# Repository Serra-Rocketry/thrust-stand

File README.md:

# thrust-stand

## 📋 Sobre

Sistema embarcado baseado em ESP32 para monitoramento de testes estáticos de motores de foguetes, com aquisição de empuxo, pressão e temperatura em tempo real, armazenamento em cartão SD e comunicação via Serial/Bluetooth.

## 🚀 Quick Start

1. Clone o repositório

```bash
git clone https://github.com/Serra-Rocketry/thrust-stand.git
```

2. Monte o hardware conforme o [mapeamento de conexões](./docs/HARDWARE.md)
3. Instale a biblioteca `Pushbutton` (Pololu) na Arduino IDE e carregue `firmware/firmware.ino` no ESP32 (placa `ESP32 Dev Module`)
4. Calibre a célula de carga com o [app de calibração](./software/config-load-cell/README.md)
5. Antes do teste, envie `TARE` e, se quiser aliviar o ESP, `BT OFF` (ver [comandos](./docs/API.md))

## 📁 Estrutura do Projeto

```
├── 📂 docs/              # Documentação técnica detalhada
├── 📂 extras/            # Utilitários extras (ex.: configuração do rádio APC220)
├── 📂 firmware/          # Código do microcontrolador ESP32
├── 📂 hardware/          # Esquemáticos, PCBs e lista de componentes
├── 📂 software/          # Ferramentas de análise e interface
└── 📂 Legacy/            # Arquivos antigos que não são mais usados
```

## 🔧 Pré-requisitos

- Hardware: ESP32 DevKit V1, célula de carga + módulo ADS1256, sensor de pressão (com divisor resistivo), termopar tipo K + módulo MAX31855, módulo microSD (SPI), botão tátil (`GPIO33` para TARE), LED com resistor de limitação, buzzer
- Software: Arduino IDE 2.0+ (core ESP32) e Python 3.10+ para o app de calibração
- Bibliotecas: ver `docs/FIRMWARE.md`

## 📖 Documentação

- [Esquemático e Montagem](./docs/HARDWARE.md)
- [Firmware e Arquitetura](./docs/FIRMWARE.md)
- [Protocolos e API](./docs/API.md)
- [Calibração da Célula de Carga](./software/config-load-cell/README.md)
- [Troubleshooting](./docs/TROUBLESHOOTING.md)
- [Evolução da Estrutura (V1 a V3)](./docs/EVOLUÇÃO_CAIXA.md)
- [Detalhes da V3](./docs/V3_DETALHES.md)
- [Arquivos Legados](./Legacy/README.md)

## 🎯 Funcionalidades

- ✅ Aquisição de empuxo e pressão a 500 Hz com ADC de 24 bits (ADS1256)
- ✅ Temperatura com termopar tipo K (MAX31855)
- ✅ Armazenamento em cartão SD com arquivos sequenciais, sem perda de amostras (gravação em núcleo separado)
- ✅ Controle local por botão (TARE)
- ✅ LED de status de gravação no SD
- ✅ Comunicação (Serial, Bluetooth), com `BT OFF` para pausar a transmissão durante o teste
- ✅ Calibração persistente da célula de carga

## 📊 Dados de Teste

Os dados de testes estáticos de motores específicos são armazenados no repositório dedicado:
[motor](https://github.com/Serra-Rocketry/motor)

Este repositório (thrust-stand) contém apenas o sistema de aquisição. Os dados coletados durante os testes devem ser commitados no repositório `motor`.

## 🤝 Contribuindo

Este projeto segue as [Boas Práticas da Serra Rocketry](https://github.com/Serra-Rocketry/best-practices). Para contribuir:

1. Fork o projeto
2. Crie uma branch para sua feature (`git checkout -b feature/AmazingFeature`)
3. Commit suas mudanças (`git commit -m 'Add some AmazingFeature'`)
4. Push para a branch (`git push origin feature/AmazingFeature`)
5. Abra um Pull Request

## ✨ Autores

- Equipe Serra Rocketry - Desenvolvimento e documentação
- Contribuidores - [Lista de contribuidores](https://github.com/Serra-Rocketry/thrust-stand/graphs/contributors)

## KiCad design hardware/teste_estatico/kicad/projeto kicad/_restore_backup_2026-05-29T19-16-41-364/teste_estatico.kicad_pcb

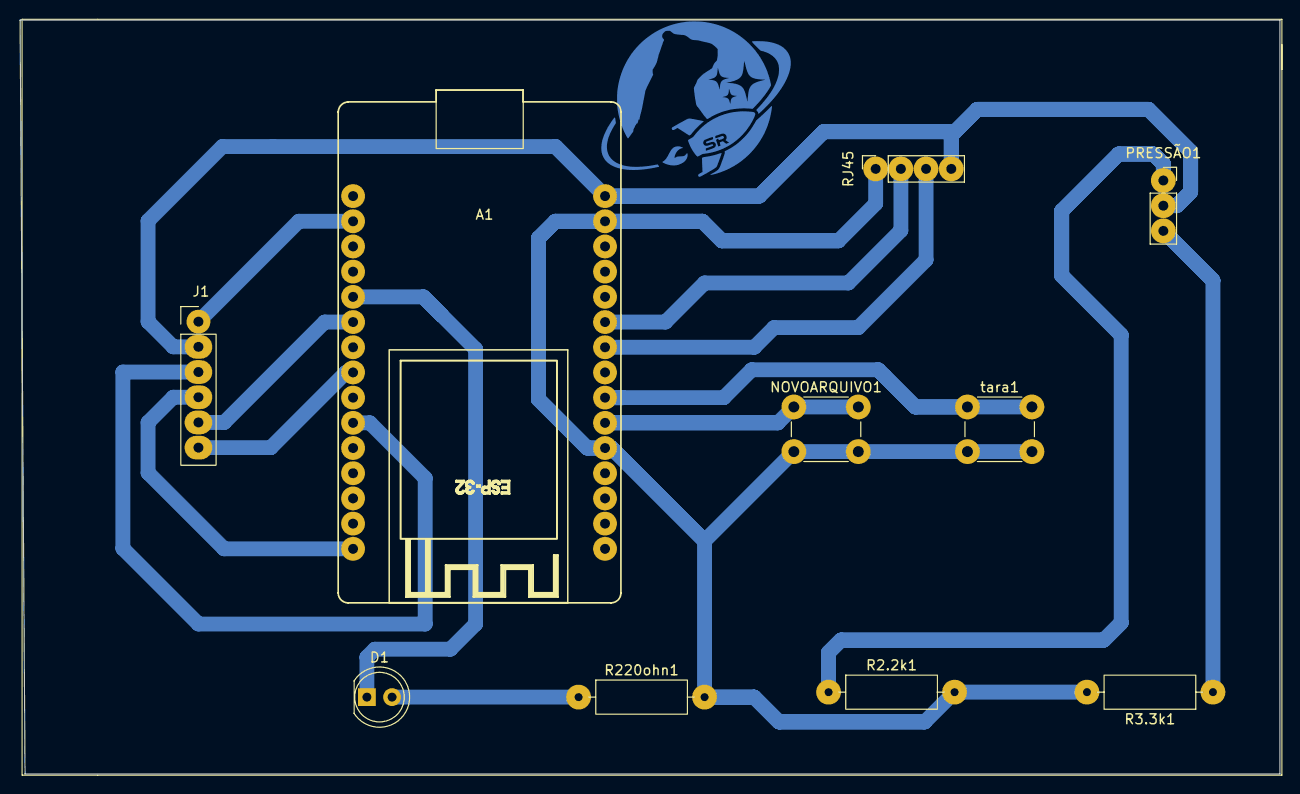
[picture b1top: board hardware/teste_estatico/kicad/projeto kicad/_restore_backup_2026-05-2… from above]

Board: 2 copper layers, 127.0 x 76.0 mm, 10 parts (0 on the bottom side), 14 nets.

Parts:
A1: ESP32_DevKit_V1_DOIT_30GPIOs; DOIT_ESP32_DEVKIT_30Pins
D1: LED; LED_D5.0mm_FlatTop
J1: PINHD_1x6_Female; PinSocket_1x06_P2.54mm_Vertical
NOVOARQUIVO1: Push_Button; SW_PUSH_6mm
PRESSÃO1: Sensor de pressão; PinSocket_1x03_P2.54mm_Vertical
R2.2k1, R3.3k1, R220ohn1: R; R_Axial_DIN0309_L9.0mm_D3.2mm_P12.70mm_Horizontal
RJ45: conexão do rj45; PinSocket_1x04_P2.54mm_Vertical
tara1: Push_Button; SW_PUSH_6mm

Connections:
unnamed: A1.21 (ADC1_CH4/D32), NOVOARQUIVO1.1
unnamed: A1.22 (ADC1_CH4/D32), tara1.1
unnamed: A1.20 (ADC1_CH7/D35), A1.29 (GND), NOVOARQUIVO1.2, R2.2k1.2, R3.3k1.2, R220ohn1.2, RJ45.1, tara1.2
unnamed: A1.25 (ADC2_CH7/D27), RJ45.2
unnamed: A1.5 (D4/ADC2_CH0), D1.1 (K)
unnamed: A1.8 (D5), J1.6
unnamed: A1.10 (D19), J1.3
unnamed: A1.15 (D23), J1.4
unnamed: A1.24 (DAC2/ADC2_CH9/D26), RJ45.3
unnamed: A1.2 (GND), J1.1
unnamed: A1.6 (RX2/GPIO16), J1.5
unnamed: A1.30 (VIN), J1.2, PRESSÃO1.2, RJ45.4
unnamed: D1.2 (A), R220ohn1.1
unnamed: PRESSÃO1.1, R2.2k1.1

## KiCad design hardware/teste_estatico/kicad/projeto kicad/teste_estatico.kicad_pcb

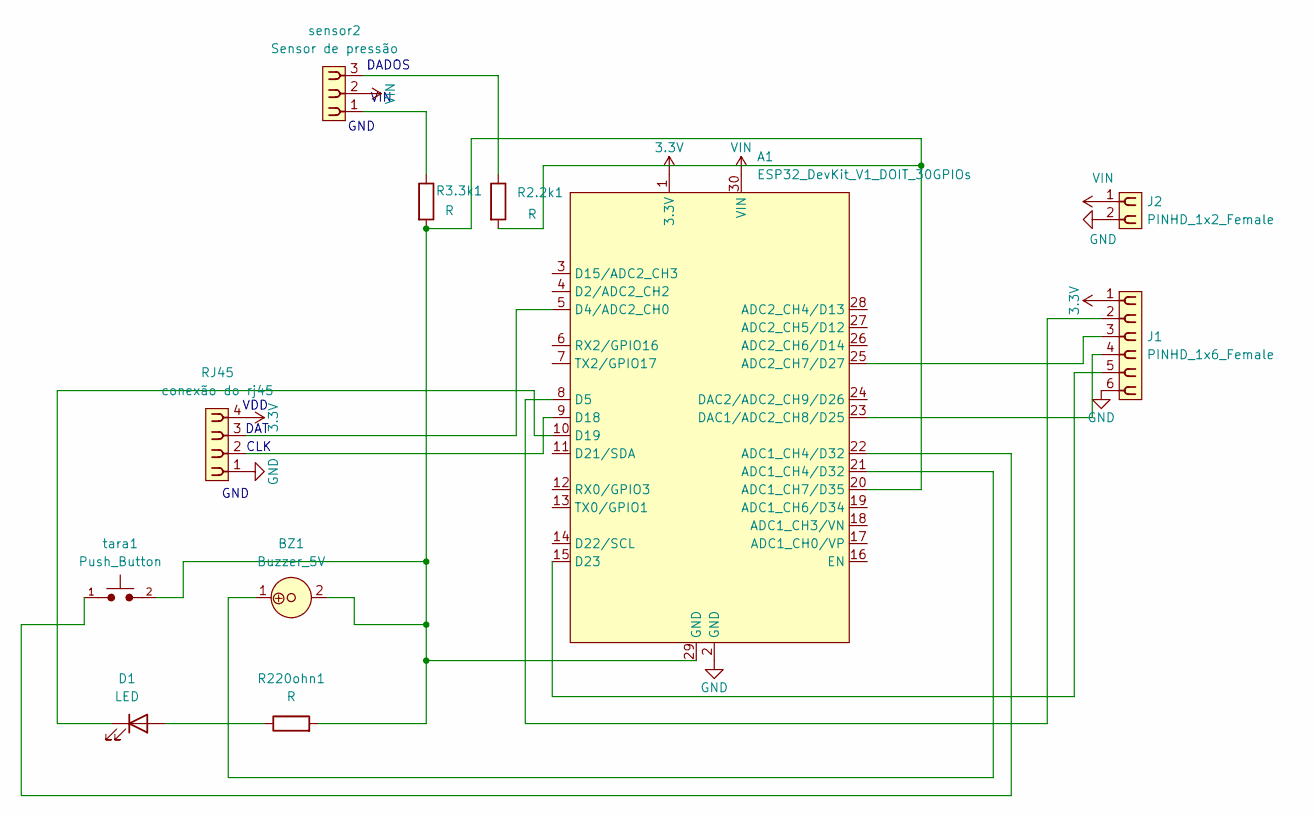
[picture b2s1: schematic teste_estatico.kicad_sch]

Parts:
A1: ESP32_DevKit_V1_DOIT_30GPIOs; DOIT_ESP32_DEVKIT_30Pins
BZ1: Buzzer_5V; MagneticBuzzer_ProSignal_ABT-410-RC
D1: LED; LED_D5.0mm_FlatTop
J1: PINHD_1x6_Female; PinSocket_1x06_P2.54mm_Vertical
J2: PINHD_1x2_Female; PinSocket_1x02_P2.54mm_Vertical
R2.2k1, R3.3k1, R220ohn1: R; R_Axial_DIN0309_L9.0mm_D3.2mm_P12.70mm_Horizontal
RJ45: conexão do rj45; PinSocket_1x04_P2.54mm_Vertical
sensor2: Sensor de pressão; PinSocket_1x03_P2.54mm_Vertical
tara1: Push_Button; SW_PUSH_6mm

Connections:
3.3V: A1.1 (3.3V), J1.1, RJ45.4
GND: A1.2 (GND), J1.6, J2.2, RJ45.1
unnamed: A1.21 (ADC1_CH4/D32), BZ1.1
unnamed: A1.22 (ADC1_CH4/D32), tara1.1
unnamed: A1.20 (ADC1_CH7/D35), A1.29 (GND), BZ1.2, R2.2k1.2, R3.3k1.2, R220ohn1.2, tara1.2
unnamed: A1.25 (ADC2_CH7/D27), J1.3
unnamed: A1.5 (D4/ADC2_CH0), RJ45.3
unnamed: A1.8 (D5), J1.2
unnamed: A1.9 (D18), RJ45.2
unnamed: A1.10 (D19), D1.1 (K)
unnamed: A1.15 (D23), J1.5
unnamed: A1.23 (DAC1/ADC2_CH8/D25), J1.4
unnamed: D1.2 (A), R220ohn1.1
unnamed: R2.2k1.1, sensor2.3
unnamed: R3.3k1.1, sensor2.1
VIN: A1.30 (VIN), J2.1, sensor2.2

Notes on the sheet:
DADOS
DAT
GND
CLK
VIN
VDD

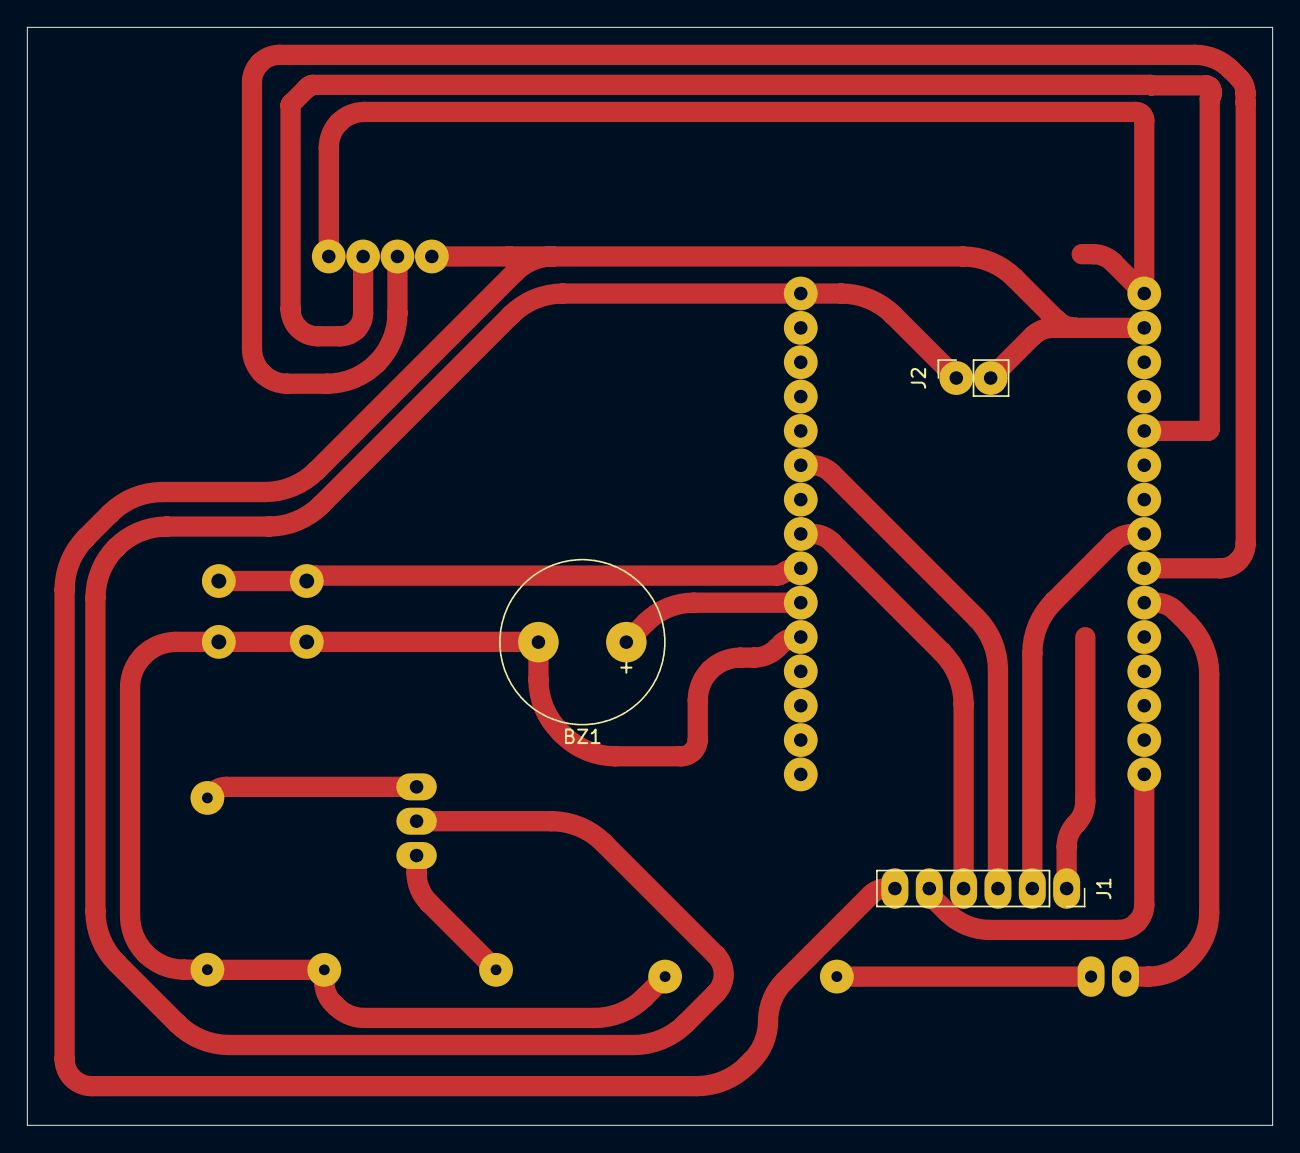
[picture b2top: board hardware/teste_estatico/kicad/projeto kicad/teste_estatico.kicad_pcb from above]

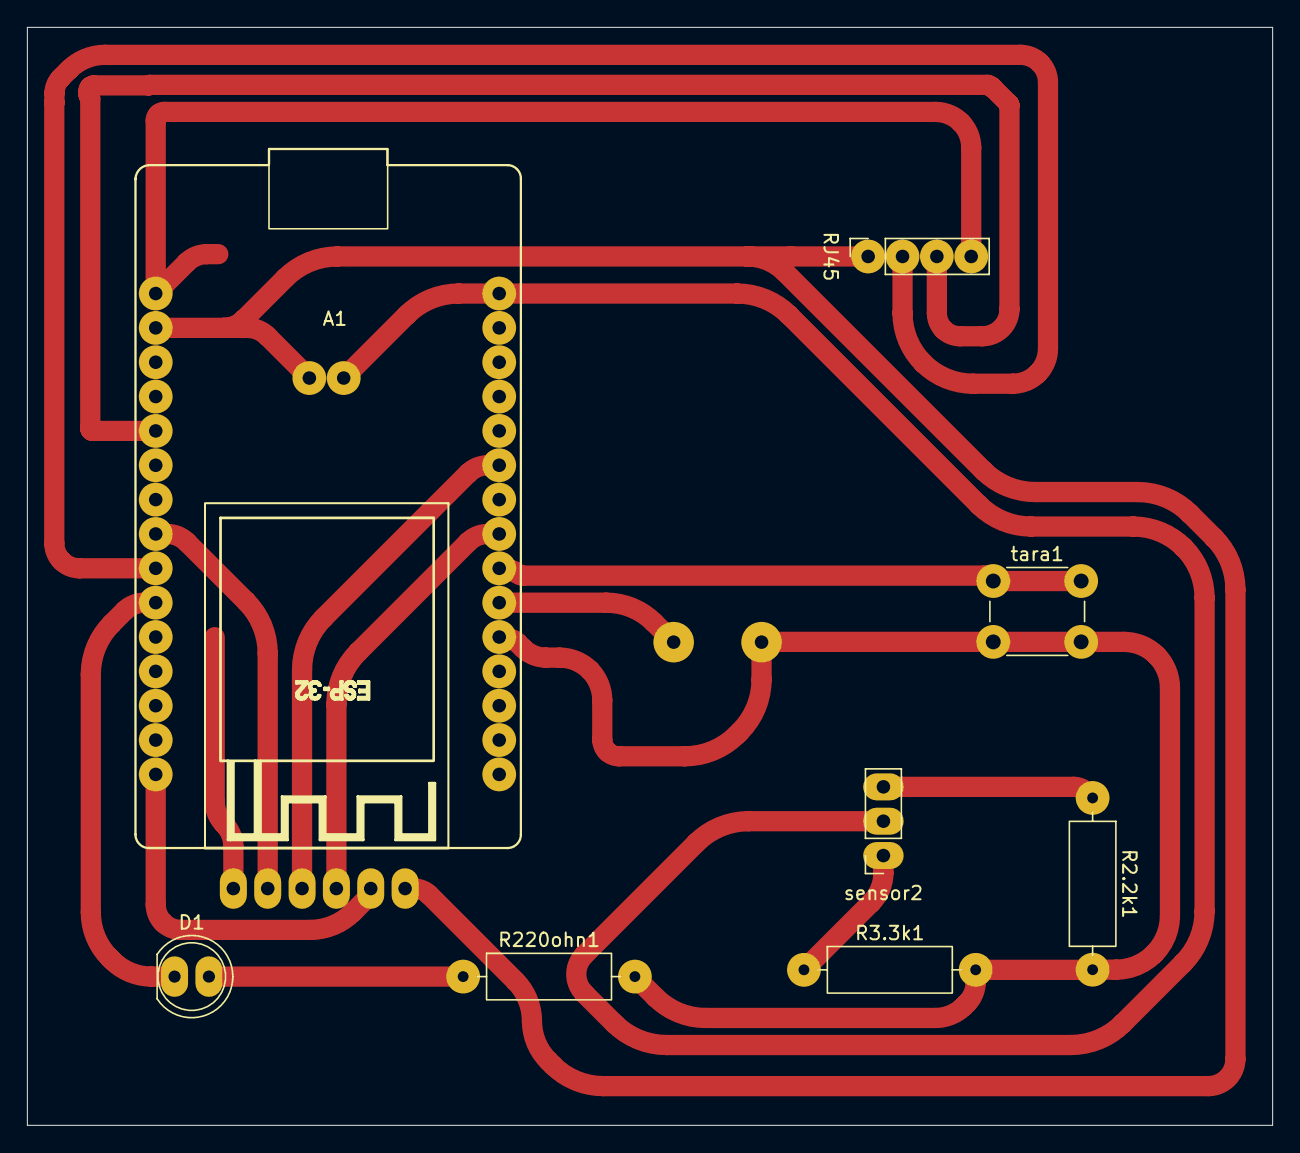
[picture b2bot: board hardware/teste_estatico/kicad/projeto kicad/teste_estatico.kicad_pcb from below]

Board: 2 copper layers, 92.1 x 81.2 mm, 11 parts (8 on the bottom side), 16 nets.
